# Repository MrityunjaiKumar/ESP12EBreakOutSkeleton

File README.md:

# ESP12EBreakOutSkeleton
##Schematic <br/>
 <br/>
##Board file <br/>
<br/>
<br/>

#Pins description wrt to vcc and gnd

Pins 	  | Hardware mapping| Hardware modules on pin
:--------:|:---------------:|:-----------------------:
v_2       | GPIO13          | MOSI
v_3       | GPIO12          | MISO
v_4       | GPIO14          |SCK
v_5       | GPIO16          |
v_6       | ADC             |
v_7       | RESET           |
g_2       | GPIO15          |SS
g_3       | GPIO29          |TX1
g_4       | GPIO4           |SDA
g_5       | GPIO5           |SCL
g_6       | RXD             |RX0
g_7       | TXD             |TX0

<br/>
#Macro Preprocessor for arduino</br>
\#define v_2 13      //GPIO13    // MOSI  <br/>
\#define v_3 12      //GPIO12    // MISO  <br/>
\#define v_4 14      //GPIO14    //SCK    <br/>
\#define v_5 16      //GPIO16             <br/>
\#define v_6 adc     //ADC                <br/>
\#define v_7 reset   //RESET              <br/>
\#define g_2 15      //GPIO15    //SS     <br/>
\#define g_3 2       //GPIO29    //TX1    <br/>
\#define g_4 4       //GPIO4     //SDA    <br/>
\#define g_5 5       //GPIO5     //SCL    <br/>
\#define g_6 rxd     //RXD       //RX0    <br/>
\#define g_7 txd     //TXD       //TX0    <br/>

<br/>
#Reference

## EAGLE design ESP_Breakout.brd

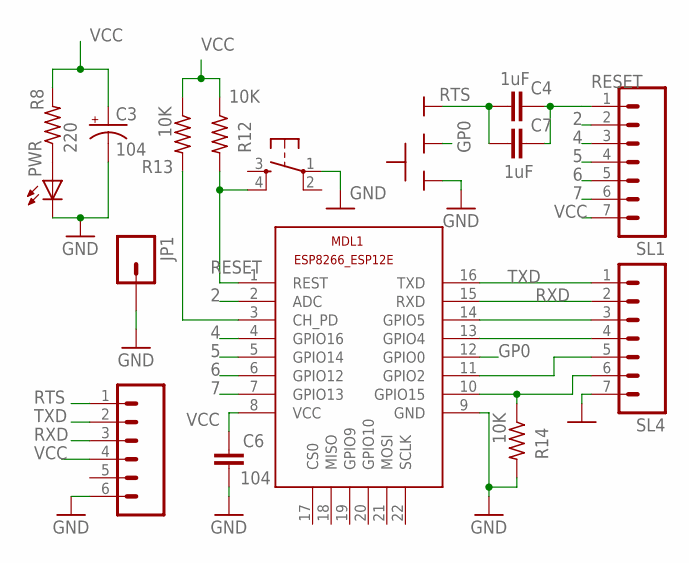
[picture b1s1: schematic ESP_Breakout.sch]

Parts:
C3: 104; C/6032-28R
C4, C7: 1uF; C1206
C6: 104; C1206
JP1: M01NOSILK-KIT; 1X01NS-KIT
MDL1: ESP8266-12EESP8266-ESP12E; ESP8266-ESP12E
PWR: LEDCHIPLED_1206; CHIPLED_1206
R8: 220; R0805
R12, R13: 10K; R0805
R14: 10K; R0603
SL1, SL4: M07; 07P
SL2: M06; 06P
U$1: SLIDESWITCH-SMALL; SMALLSWITCH
U$2: OMRON_SWITCH_10-XX; B3F-10XX

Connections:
2: MDL1.2 (ADC), SL1.2
4: MDL1.4 (GPIO16), SL1.3
5: MDL1.5 (GPIO14), SL1.4
6: MDL1.6 (GPIO12), SL1.5
7: MDL1.7 (GPIO13), SL1.6
BLED: MDL1.10 (GPIO15), R14.1, SL4.6
GND: C3.-, C6.2, JP1.1, MDL1.9 (GND), PWR.C, R14.2, SL2.6, SL4.7, U$1.1, U$2.1
GP0: MDL1.12 (GPIO0), U$1.2
unnamed: MDL1.14 (GPIO5), SL4.3
unnamed: MDL1.13 (GPIO4), SL4.4
unnamed: PWR.A, R8.1
unnamed: MDL1.11 (GPIO2), SL4.5
unnamed: MDL1.3 (CH_PD), R13.2
RESET: C4.2, C7.2, MDL1.1 (REST), R12.2, SL1.1, U$2.4 (S1)
RTS: C4.1, C7.1, SL2.1, U$1.3
RXD: MDL1.15 (RXD), SL2.3, SL4.2
TXD: MDL1.16 (TXD), SL2.2, SL4.1
VCC: C3.+, C6.1, MDL1.8 (VCC), R8.2, R12.1, R13.1, SL1.7, SL2.4

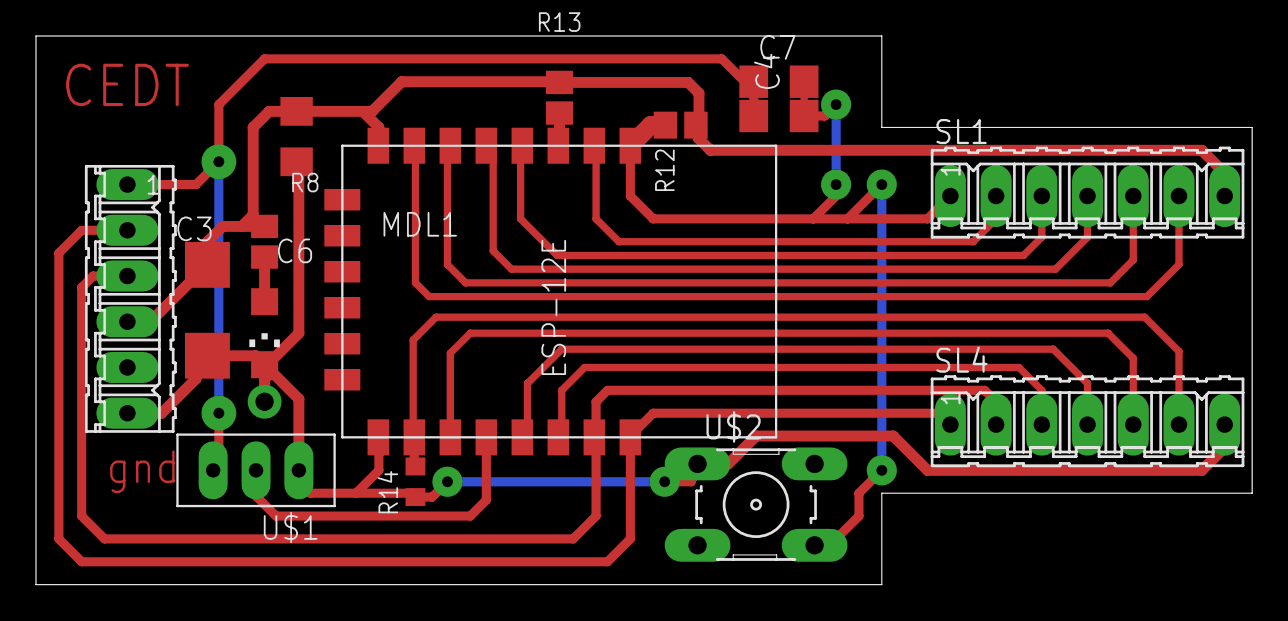
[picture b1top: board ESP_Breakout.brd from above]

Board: 2 copper layers, 67.6 x 30.5 mm, 16 parts (0 on the bottom side), 18 nets.

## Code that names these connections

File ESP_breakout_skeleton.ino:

#define v_2 13//GPIO13
#define v_3 12//GPIO12
#define v_4 14//GPIO14
#define v_5 16//GPIO16
#define v_6 adc//ADC
#define v_7 reset//RESET
#define g_2 15//GPIO15 
#define g_3 2//GPIO29
#define g_4 4//GPIO4
#define g_5 5//GPIO5
#define g_6 rxd//RXD
#define g_7 txd//TXD

int digital_pins[]={v_2,v_3,v_4,v_5,g_2,g_3,g_4,g_5};

void setup() {
  // put your setup code here, to run once:
   for(int i=0;i<8;i++){
    pinMode(digital_pins[i],OUTPUT);
    }
}
void toggle(int x){
  digitalWrite(x,HIGH);
  delay(200);
  digitalWrite(x,LOW);
  delay(200);
  }
void loop() {
  // put your main code here, to run repeatedly:
  for(int i=0;i<8;i++){
    toggle(digital_pins[i]);
    }
}

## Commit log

2016-12-02 name of pins updated
2016-12-02 board and schematic file added
2016-12-02 board image added
2016-12-02 Readme modified
2016-12-02 Create LICENSE.md
    license added
2016-12-05 readme updated

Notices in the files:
parts and their libraries:
SparkFun-Connectors: Licensing: Creative Commons ShareAlike 4.0 International - https://creativecommons.org/licenses/by-sa/4.0
